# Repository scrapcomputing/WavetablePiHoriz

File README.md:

# Horizontal WavetablePi

This is the horizontal version of [WavetablePi](https://github.com/scrapcomputing/WavetablePi).
It is a wavetable module based on the Raspberry Pi Zero 2 W running [mt32-pi](https://github.com/dwhinham/mt32-pi).
It is capable of emulating several midi synthesizers, including mt32, sc55 and general midi with custom sound fonts.
For a complete feature list please refer to the [mt32-pi](https://github.com/dwhinham/mt32-pi) project.

### Assembling the Horizontal WavetablePi (by sweetlilmre)
An assembly guide can be found [here](assembly.md).

</p>

- 5.25 drive bay faceplates (by Michael Swimm) https://www.thingiverse.com/thing:6652143

# New Features
- This version also includes headers for the mt32-pi buttons and rotary encoder.

# Bill of materials

The gerber can be found in the [releases](https://github.com/scrapcomputing/WavetablePiHoriz/releases)

Item                                     | #   | Description
-----------------------------------------|-----|-----------------------------------------
Raspberry Pi Zero 2 W                    | 1   | The older RPi Zero is not fast enough
40-pin 2x20 male header 2.54mm pitch     | 1   | For attaching the RPi to the board.
26-pin 2x13 female header 2.54mm pitch   | 1   | For attaching the board to the wavetable header
6-pin 2x3 pin male header 2.54mm pitch   | 1   | For the audio select jumpers
2-pin 1x2 pin male header 2.54mm pitch   | 4   | (Optional) Headers for mt32-pi buttons
5-pin 1x5 pin male header 2.54mm pitch   | 1   | (Optional) Header for mt32-pi rotary encoder
Jumper 2.54mm pitch                      | 2   | Jumpers for the audio selection header
Capacitor 10uF through-hole ceramic      | 2   |
Capacitor 100nF through-hole ceramic     | 2   | C3 and C4 which form the PWM audio low-pass filter along with R3 and R4. 100nF is for a 1.6KHz cutoff frequency. Use lower values for higher cutoff
Resistor 22K Ohm                         | 1   |
Resistor 10K Ohm                         | 1   |
Resistor 1K Ohm                          | 2   | R3 and R4, which along with C3 and C4 form a low-pass filter of the PWM audio
0.91 OLED SSD1306 I2C 128x32 module      | 1   | (Optional)
PCM5102A I2S DAC Module (aka GY PCM5120) | 1   | (Optional but highly recommended) Please check the PCB for the supported dimensions and form factor!

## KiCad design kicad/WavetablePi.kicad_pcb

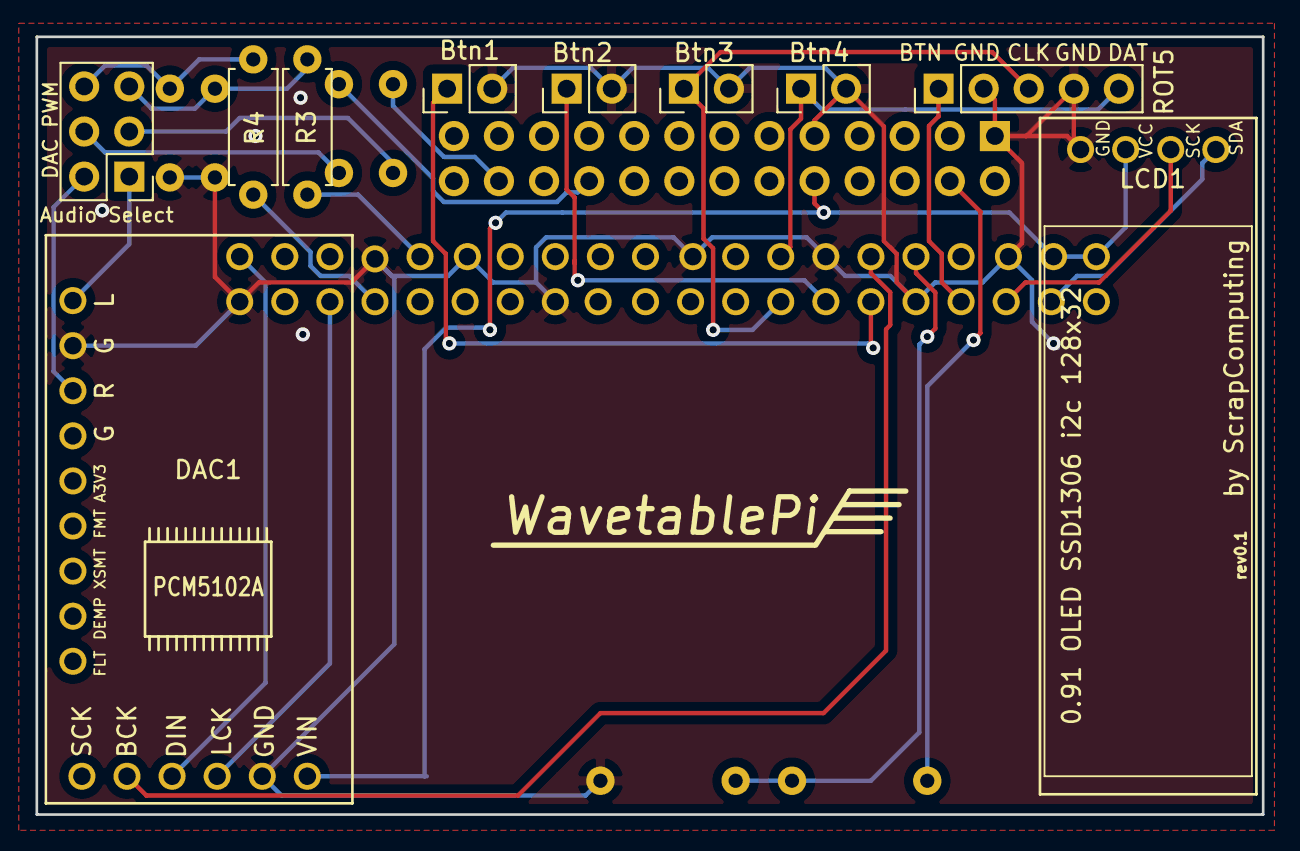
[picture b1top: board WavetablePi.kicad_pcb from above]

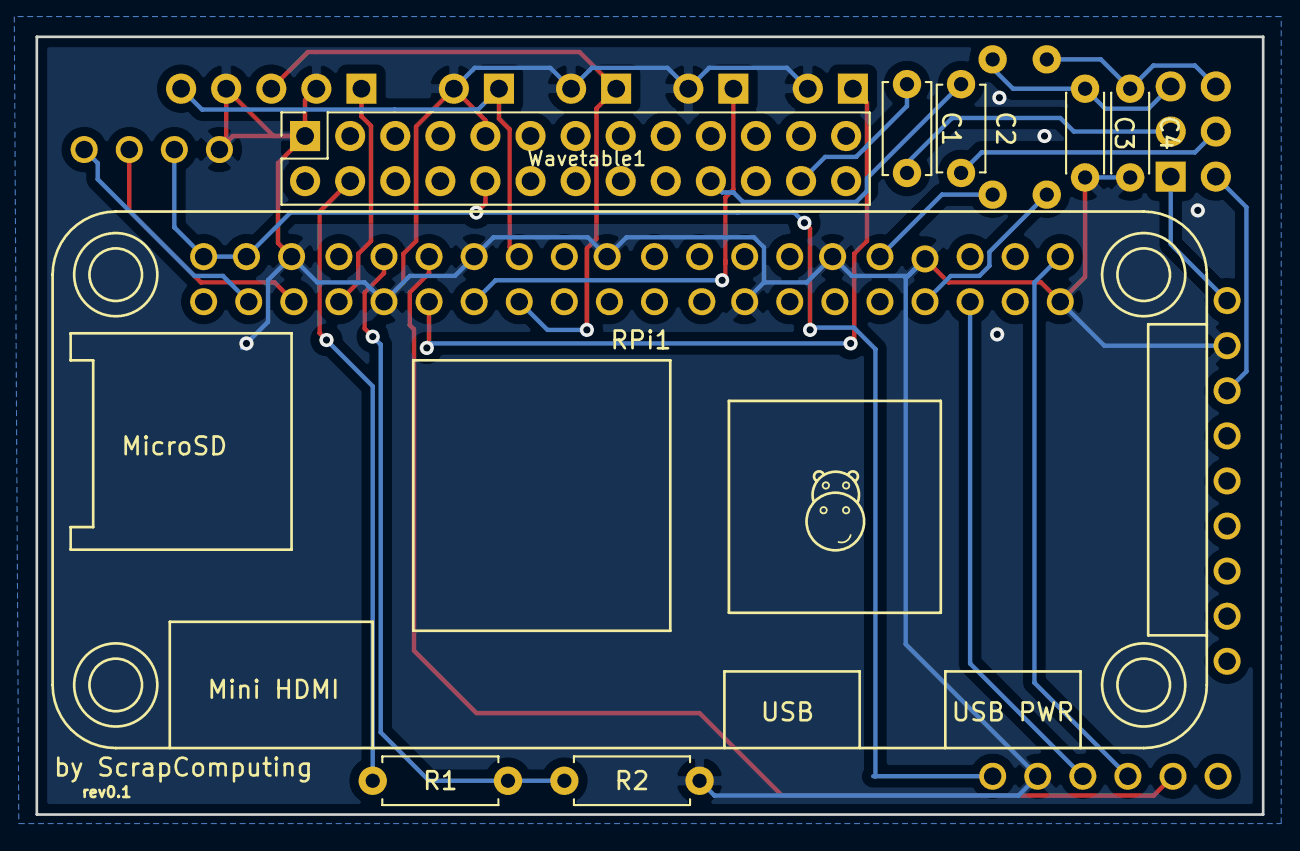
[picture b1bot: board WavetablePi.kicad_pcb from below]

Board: 2 copper layers, 69.1 x 43.8 mm, 18 parts (8 on the bottom side), 24 nets.

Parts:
Audio_Select1: Conn_02x03_Odd_Even; PinHeader_2x03_P2.54mm_Vertical
Btn1: Btn1; PinHeader_1x02_P2.54mm_Vertical
Btn2: Btn2; PinHeader_1x02_P2.54mm_Vertical
Btn3: Btn3; PinHeader_1x02_P2.54mm_Vertical
Btn4: Btn4; PinHeader_1x02_P2.54mm_Vertical
C1: 10uF; C_Disc_D5.0mm_W2.5mm_P5.00mm
C2: 10uF; C_Disc_D4.7mm_W2.5mm_P5.00mm
C3, C4: 100nF; C_Disc_D4.3mm_W1.9mm_P5.00mm
DAC1: GY_PCM5102A
LCD1: LCD_0.91_OLED
R1: 10K; R_Axial_DIN0207_L6.3mm_D2.5mm_P7.62mm_Horizontal
R2: 22K; R_Axial_DIN0207_L6.3mm_D2.5mm_P7.62mm_Horizontal
R3, R4: 1K; R_Axial_DIN0207_L6.3mm_D2.5mm_P7.62mm_Horizontal
ROT5: ROTARY; PinHeader_1x05_P2.54mm_Vertical
RPi1: RPiZero2W
Wavetable1: Conn_02x13_Odd_Even; PinSocket_2x13_P2.54mm_Vertical

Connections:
+5V: DAC1.6, LCD1.3, RPi1.2, RPi1.4, Wavetable1.10
GND: Btn1.2, Btn2.2, Btn3.2, Btn4.2, C3.2, C4.2, DAC1.5, DAC1.14, LCD1.4, R2.2, ROT5.2, ROT5.4, RPi1.6, RPi1.9, RPi1.14, RPi1.20, RPi1.25, RPi1.30, RPi1.34, RPi1.39, Wavetable1.1, Wavetable1.9
GP4: ROT5.1, RPi1.7
GP17: Btn1.1, RPi1.11
GP22: Btn3.1, ROT5.3, RPi1.15
GP23: Btn4.1, ROT5.5, RPi1.16
GP27: Btn2.1, RPi1.13
unnamed: Audio_Select1.1, DAC1.15
unnamed: Audio_Select1.2, DAC1.13
unnamed: Audio_Select1.3, C1.2
unnamed: Audio_Select1.4, C2.2
unnamed: Audio_Select1.5, C3.1, R3.1
unnamed: Audio_Select1.6, C4.1, R4.1
unnamed: C1.1, Wavetable1.24
unnamed: C2.1, Wavetable1.20
unnamed: DAC1.2, RPi1.12
unnamed: DAC1.3, RPi1.40
unnamed: DAC1.4, RPi1.35
unnamed: LCD1.1, RPi1.3
unnamed: LCD1.2, RPi1.5
unnamed: R1.1, R2.1, RPi1.10
unnamed: R1.2, Wavetable1.4
unnamed: R3.2, RPi1.32
unnamed: R4.2, RPi1.33

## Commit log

2024-05-12 Rev 0.1
2024-06-11 README update
2024-09-12 Added assembly guide
2024-09-12 fixed some image alignment
2024-09-13 added attribution header
